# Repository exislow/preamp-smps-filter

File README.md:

# SMPS HF Filter

Original idead and almost exact copy source: https://www.diyaudio.com/forums/analog-line-level/354213-po89zb-inline-dc-filter-smps-wall-warts-preamps-hpa-korg-nutube-etc.html#post6197841

The only difference are the mounting wholes and slightly different traces (no improvement intendent.)

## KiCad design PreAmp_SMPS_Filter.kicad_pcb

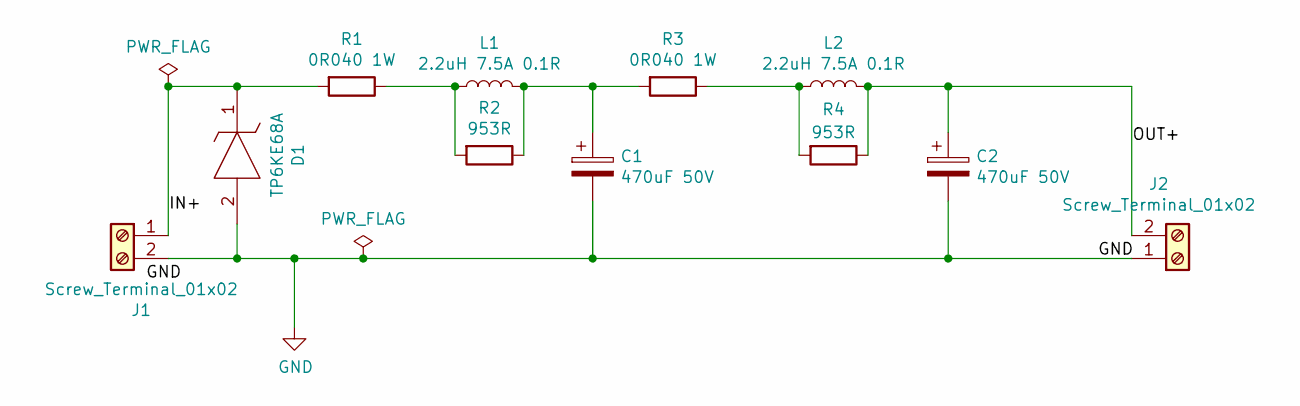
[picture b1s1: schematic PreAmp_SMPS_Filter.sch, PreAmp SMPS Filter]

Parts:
C1, C2: 470uF 50V; CP_Radial_D10.0mm_P5.00mm
D1: TP6KE68A; DIOAD1910W86L670D310; Manufacturer_Part_Number TP6KE68A; Mouser Part Number 576-TP6KE68A
J1, J2: Screw_Terminal_01x02; TerminalBlock_Phoenix_MKDS-1,5-2_1x02_P5.00mm_Horizontal
L1, L2: 2.2uH 7.5A 0.1R; L_Radial_D8.7mm_P5.00mm_Fastron_07HCP
R1, R3: 0R040 1W; R_Bare_Metal_Element_L12.4mm_W4.8mm_P11.40mm
R2, R4: 953R; R_Axial_DIN0207_L6.3mm_D2.5mm_P10.16mm_Horizontal

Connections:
/IN+: D1.1, J1.1, R1.2
/OUT+: C2.1, J2.2, L2.2, R4.1
GND: C1.2, C2.2, D1.2, J1.2, J2.1
unnamed: C1.1, L1.2, R2.1, R3.2
unnamed: L1.1, R1.1, R2.2
unnamed: L2.1, R3.1, R4.2

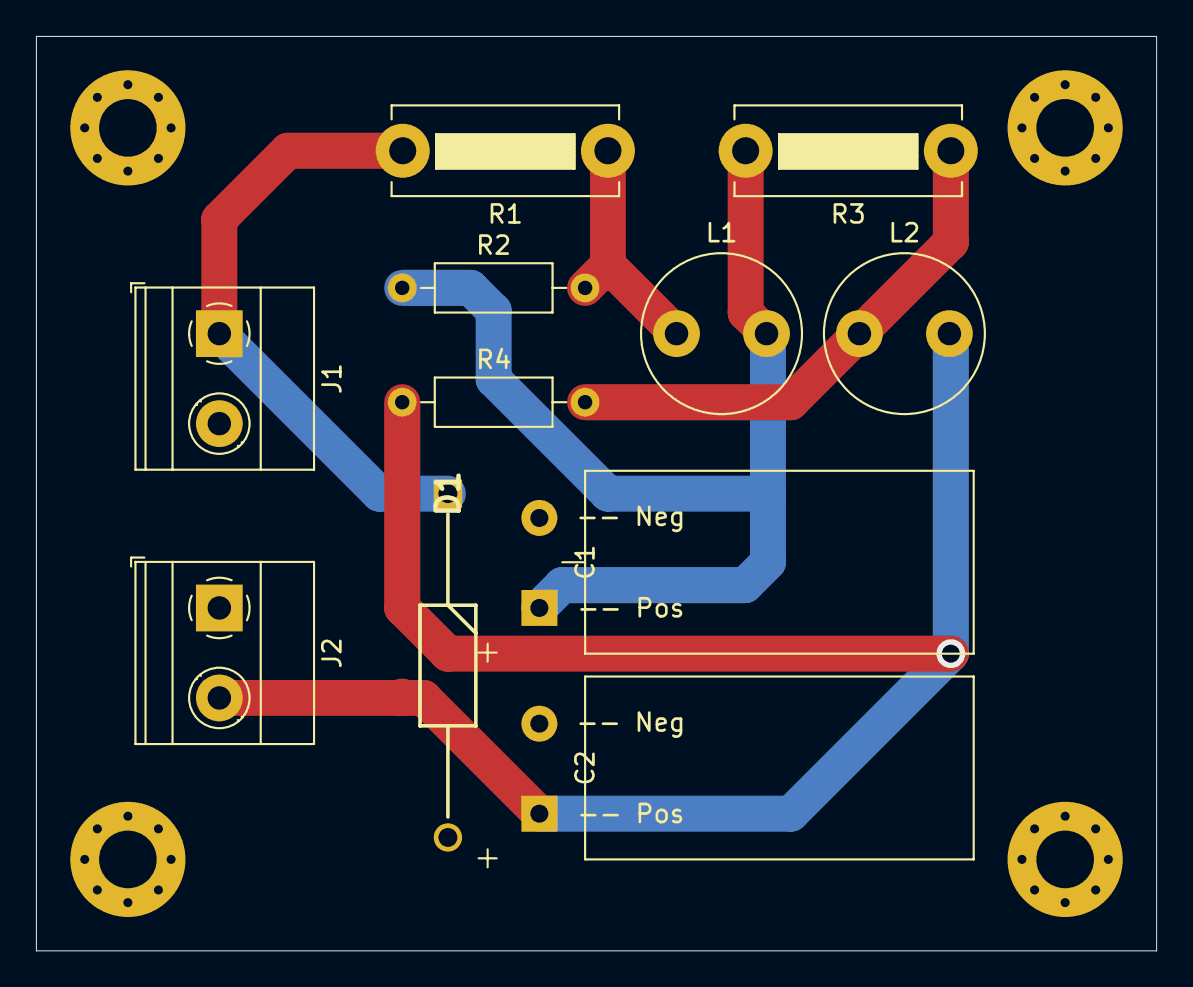
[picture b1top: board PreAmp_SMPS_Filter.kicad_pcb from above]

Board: 2 copper layers, 62.2 x 50.8 mm, 11 parts (0 on the bottom side), 6 nets.

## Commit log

2021-05-14 Initial commit.
2021-05-14 Typo in readme
